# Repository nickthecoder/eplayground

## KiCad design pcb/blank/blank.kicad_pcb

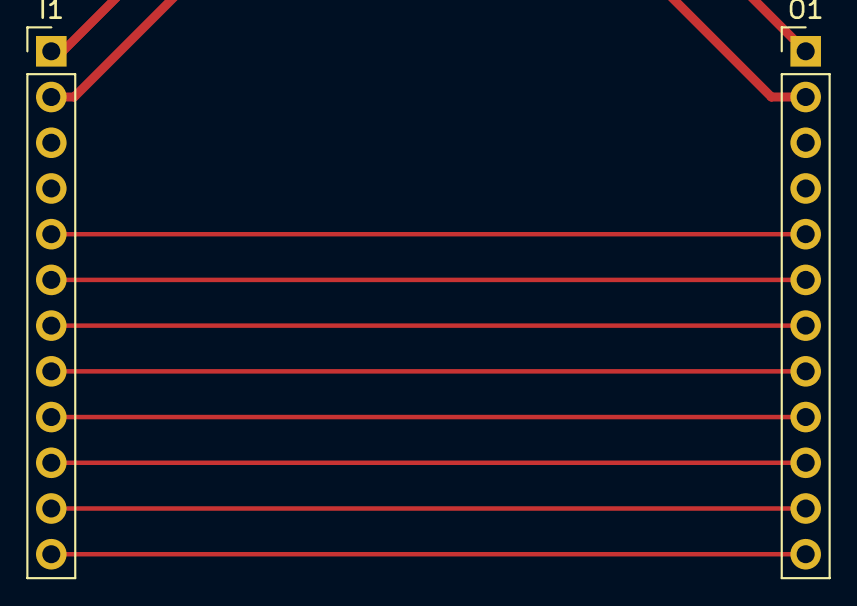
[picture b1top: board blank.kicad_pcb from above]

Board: 2 copper layers, 4 parts (0 on the bottom side), 11 nets.

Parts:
I1: Input; Pin_Header_Straight_1x12_Pitch2.54mm
M3, M3#2: MountingHole_3.2mm_M3
O1: Output; Socket_Strip_Straight_1x12_Pitch2.54mm

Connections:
/L0: I1.5, O1.5
/L1: I1.6, O1.6
/L2: I1.7, O1.7
/L3: I1.8, O1.8
/L4: I1.9, O1.9
/L5: I1.10, O1.10
/L6: I1.11, O1.11
/L7: I1.12, O1.12
/VCC: I1.2, O1.2
/VIN: I1.1, O1.1
Earth: I1.3, O1.3

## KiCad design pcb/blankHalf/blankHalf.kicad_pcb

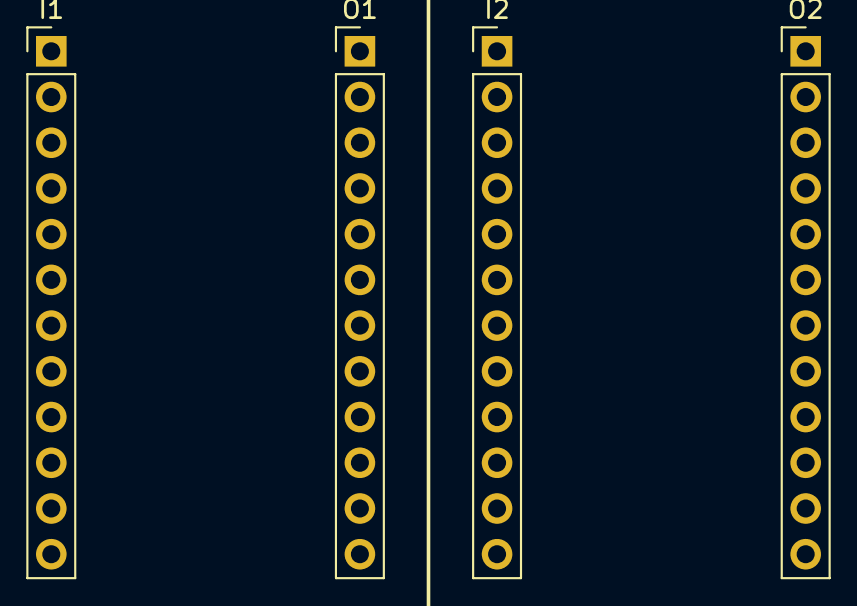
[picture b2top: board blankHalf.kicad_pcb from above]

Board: 2 copper layers, 6 parts (0 on the bottom side), 22 nets, no tracks yet.

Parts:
I1, I2: Input; Pin_Header_Straight_1x12_Pitch2.54mm
M3, M3#2: MountingHole_3.2mm_M3
O1, O2: Output; Socket_Strip_Straight_1x12_Pitch2.54mm

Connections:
/D0: I2.5, O2.5
/D1: I2.6, O2.6
/D2: I2.7, O2.7
/D3: I2.8, O2.8
/D4: I2.9, O2.9
/D5: I2.10, O2.10
/D6: I2.11, O2.11
/D7: I2.12, O2.12
/GND2: I2.3, O2.3
/L0: I1.5, O1.5
/L1: I1.6, O1.6
/L2: I1.7, O1.7
/L3: I1.8, O1.8
/L4: I1.9, O1.9
/L5: I1.10, O1.10
/L6: I1.11, O1.11
/L7: I1.12, O1.12
/VCC: I1.2, O1.2
/VCC2: I2.2, O2.2
/VIN: I1.1, O1.1
/VIN2: I2.1, O2.1
Earth: I1.3, O1.3

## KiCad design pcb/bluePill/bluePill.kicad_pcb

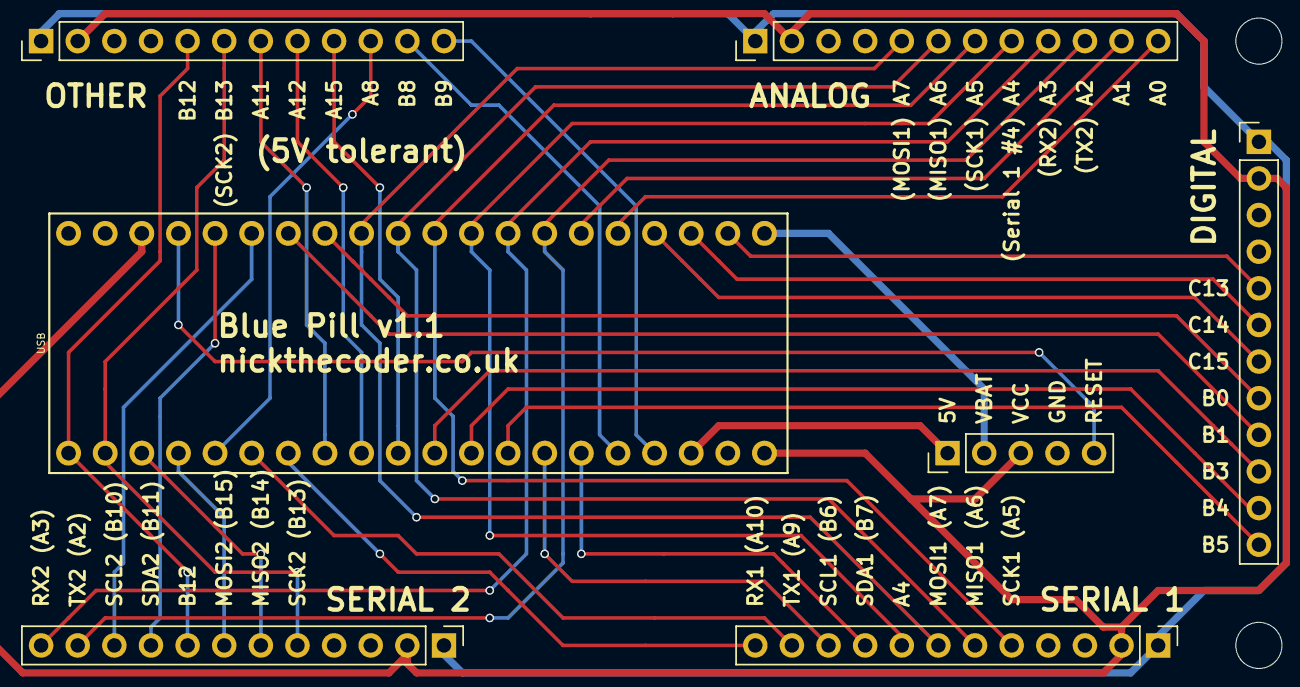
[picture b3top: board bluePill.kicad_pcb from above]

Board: 2 copper layers, 9 parts (0 on the bottom side), 38 nets.

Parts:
J3: Power; Pin_Header_Straight_1x05_Pitch2.54mm
O1, O5: SerialOutput; Socket_Strip_Straight_1x12_Pitch2.54mm
O2, O3, O4: Output; Socket_Strip_Straight_1x12_Pitch2.54mm
U1: BluePill; bluePill
X: M3; MountingHole_3.2mm_M3
X#2: M3; MountingHole_3.2mm_M3

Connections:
/5V: J3.1, U1.38
/A0: O3.12, U1.5
/A1: O3.11, U1.6
/A2: O3.10, O5.11, U1.7
/A3: O3.9, O5.12, U1.8
/A4: O1.8, O3.8, U1.9
/A5: O1.5, O3.7, U1.10
/A6: O1.6, O3.6, U1.11
/A7: O1.7, O3.5, U1.12
/A8: O4.10, U1.25
/A9: O1.11, U1.26
/A10: O1.12, U1.27
/A11: O4.7, U1.28
/A12: O4.8, U1.29
/A15: O4.9, U1.30
/B0: O2.8, U1.13
/B1: O2.9, U1.14
/B3: O2.10, U1.31
/B4: O2.11, U1.32
/B5: O2.12, U1.33
/B6: O1.10, U1.34
/B7: O1.9, U1.35
/B8: O4.11, U1.36
/B9: O4.12, U1.37
/B10: O5.10, U1.15
/B11: O5.9, U1.16
/B12: O4.5, O5.8, U1.21
/B13: O4.6, O5.5, U1.22
/B14: O5.6, U1.23
/B15: O5.7, U1.24
/C13: O2.5, U1.2
/C14: O2.6, U1.3
/C15: O2.7, U1.4
/GND: J3.4, O1.3, O2.3, O3.3, O4.3, O5.3, U1.19, U1.20, U1.39
/RESET: J3.5, U1.17
/VBAT: J3.2, U1.1
/VCC: J3.3, O1.2, O2.2, O3.2, O4.2, O5.2, U1.18, U1.40
/VIN: O1.1, O2.1, O3.1, O4.1, O5.1

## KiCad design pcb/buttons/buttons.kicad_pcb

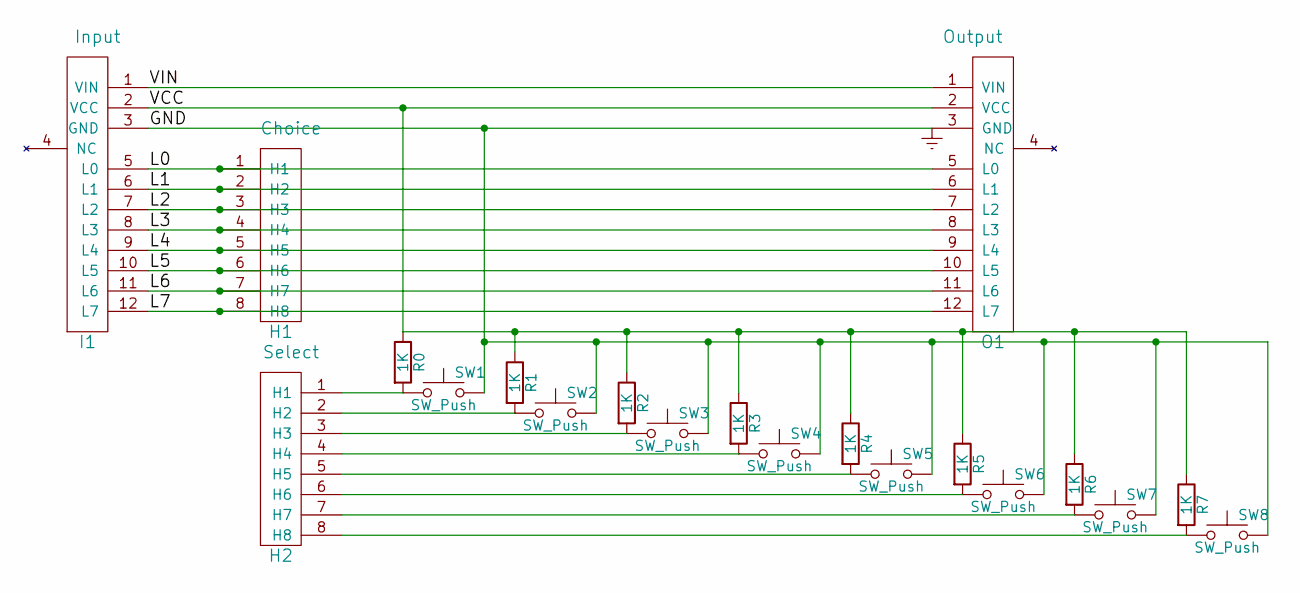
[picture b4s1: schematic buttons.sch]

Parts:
H1: Choice; Pin_Header_Straight_1x08_Pitch2.54mm
H2: Select; Pin_Header_Straight_1x08_Pitch2.54mm
I1: Input; Pin_Header_Straight_1x12_Pitch2.54mm
O1: Output; Pin_Header_Straight_1x12_Pitch2.54mm
R0, R1, R2, R3, R4, R5, R6, R7: 1K; R_Axial_DIN0204_L3.6mm_D1.6mm_P7.62mm_Horizontal
SW1, SW2, SW3, SW4, SW5, SW6, SW7, SW8: SW_Push; SW_PUSH_6mm

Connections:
/L0: H1.1 (H1), I1.5 (L0), O1.5 (L0)
/L1: H1.2 (H2), I1.6 (L1), O1.6 (L1)
/L2: H1.3 (H3), I1.7 (L2), O1.7 (L2)
/L3: H1.4 (H4), I1.8 (L3), O1.8 (L3)
/L4: H1.5 (H5), I1.9 (L4), O1.9 (L4)
/L5: H1.6 (H6), I1.10 (L5), O1.10 (L5)
/L6: H1.7 (H7), I1.11 (L6), O1.11 (L6)
/L7: H1.8 (H8), I1.12 (L7), O1.12 (L7)
/VCC: I1.2 (VCC), O1.2 (VCC), R0.1, R1.1, R2.1, R3.1, R4.1, R5.1, R6.1, R7.1
/VIN: I1.1 (VIN), O1.1 (VIN)
Earth: I1.3 (GND), O1.3 (GND), SW1.2, SW2.2, SW3.2, SW4.2, SW5.2, SW6.2, SW7.2, SW8.2
unnamed: H2.1 (H1), R0.2, SW1.1
unnamed: H2.2 (H2), R1.2, SW2.1
unnamed: H2.3 (H3), R2.2, SW3.1
unnamed: H2.4 (H4), R3.2, SW4.1
unnamed: H2.5 (H5), R4.2, SW5.1
unnamed: H2.6 (H6), R5.2, SW6.1
unnamed: H2.7 (H7), R6.2, SW7.1
unnamed: H2.8 (H8), R7.2, SW8.1

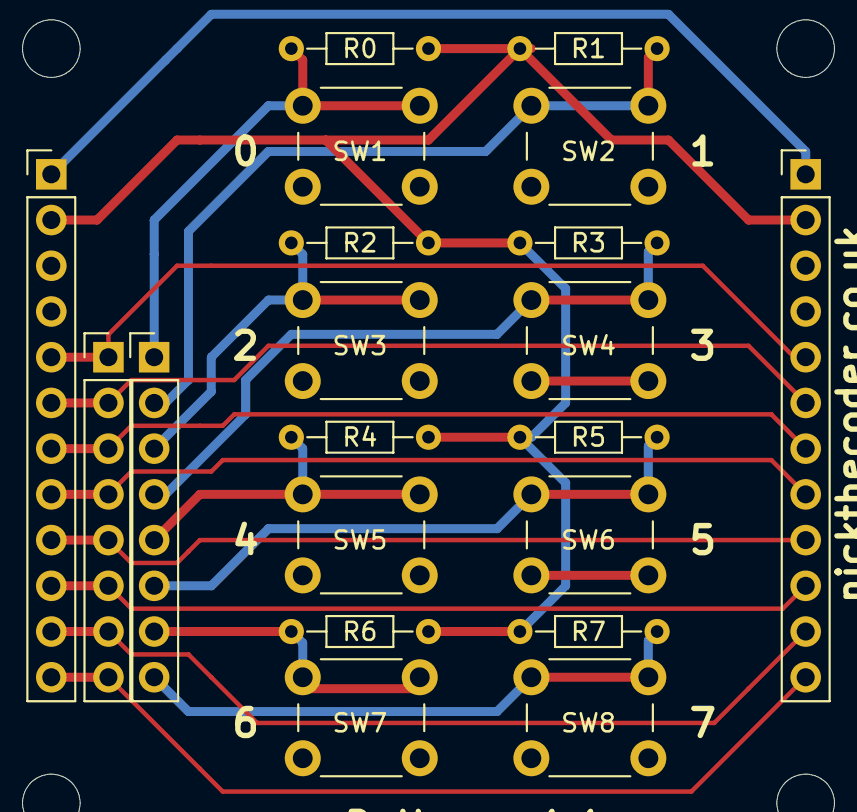
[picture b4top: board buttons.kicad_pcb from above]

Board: 2 copper layers, 22 parts (0 on the bottom side), 19 nets.

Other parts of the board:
M3, M3#2: MountingHole_3.2mm_M3

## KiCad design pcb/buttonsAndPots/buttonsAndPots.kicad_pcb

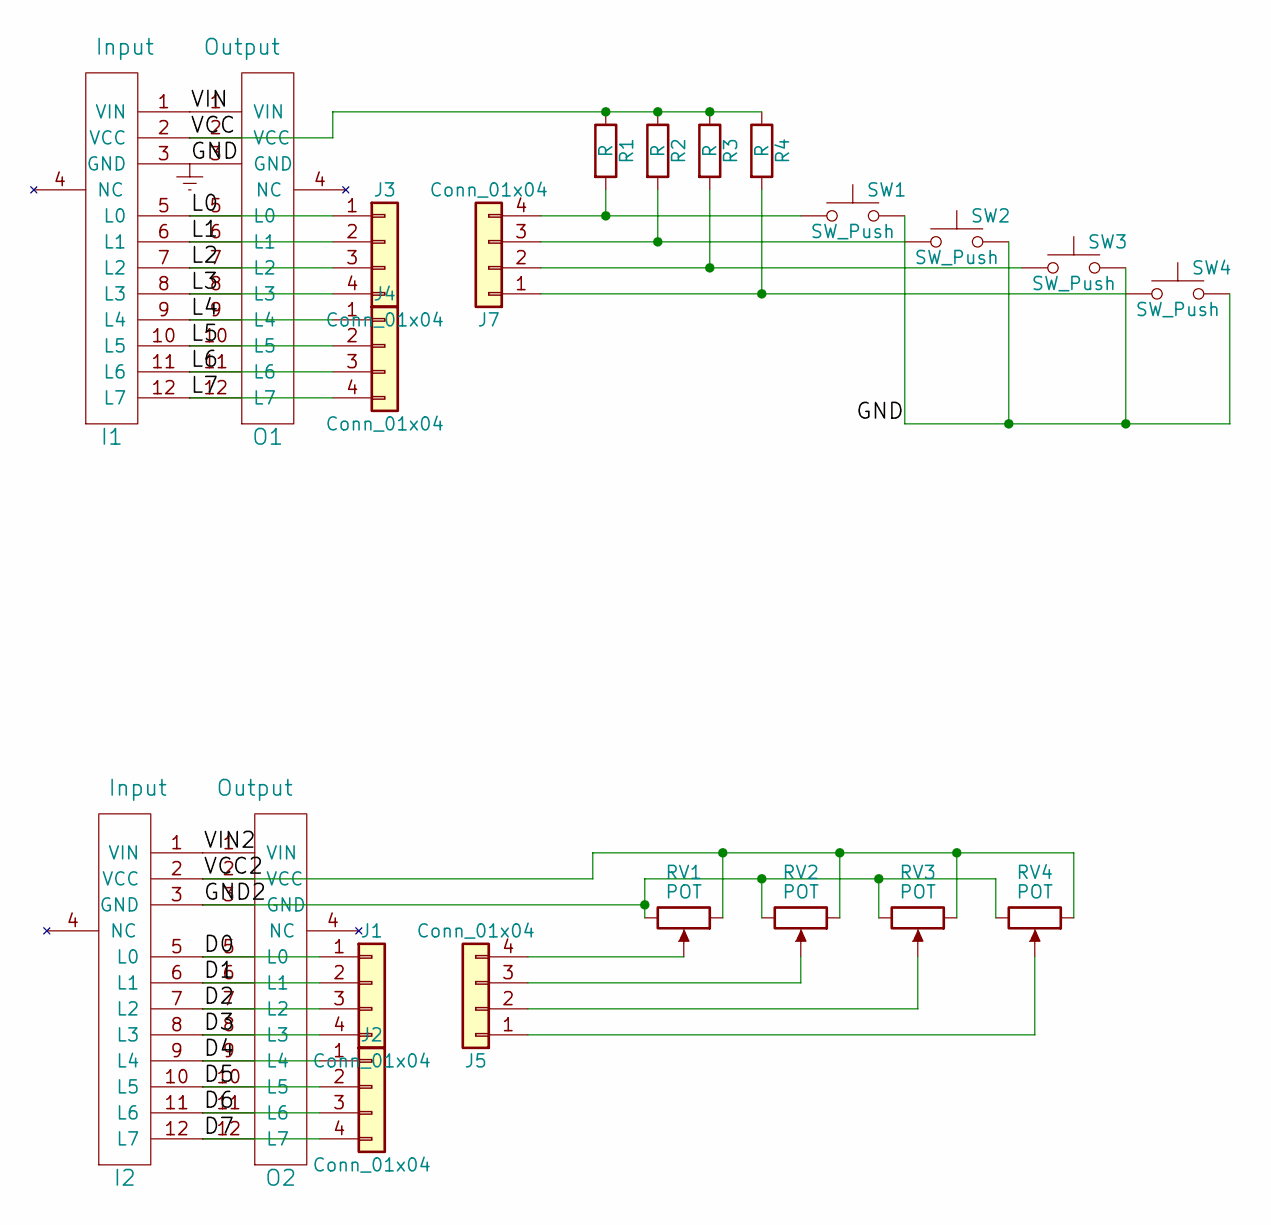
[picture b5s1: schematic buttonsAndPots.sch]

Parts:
I1, I2: Input; Pin_Header_Straight_1x12_Pitch2.54mm
J1, J2, J3, J4, J5, J7: Conn_01x04; Pin_Header_Straight_1x04_Pitch2.54mm
O1, O2: Output; Socket_Strip_Straight_1x12_Pitch2.54mm
R1, R2, R3, R4: R; R_Axial_DIN0204_L3.6mm_D1.6mm_P7.62mm_Horizontal
RV1, RV2, RV3, RV4: POT; Potentiometer_Trimmer_Piher_PT-10v10_Horizontal_Px10.0mm_Py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
SW1, SW2, SW3, SW4: SW_Push; SW_PUSH_6mm

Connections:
/D0: I2.5 (L0), J1.1, O2.5 (L0)
/D1: I2.6 (L1), J1.2, O2.6 (L1)
/D2: I2.7 (L2), J1.3, O2.7 (L2)
/D3: I2.8 (L3), J1.4, O2.8 (L3)
/D4: I2.9 (L4), J2.1, O2.9 (L4)
/D5: I2.10 (L5), J2.2, O2.10 (L5)
/D6: I2.11 (L6), J2.3, O2.11 (L6)
/D7: I2.12 (L7), J2.4, O2.12 (L7)
/GND2: I2.3 (GND), O2.3 (GND), RV1.3, RV2.3, RV3.3, RV4.3
/L0: I1.5 (L0), J3.1, O1.5 (L0)
/L1: I1.6 (L1), J3.2, O1.6 (L1)
/L2: I1.7 (L2), J3.3, O1.7 (L2)
/L3: I1.8 (L3), J3.4, O1.8 (L3)
/L4: I1.9 (L4), J4.1, O1.9 (L4)
/L5: I1.10 (L5), J4.2, O1.10 (L5)
/L6: I1.11 (L6), J4.3, O1.11 (L6)
/L7: I1.12 (L7), J4.4, O1.12 (L7)
/VCC: I1.2 (VCC), O1.2 (VCC), R1.1, R2.1, R3.1, R4.1
/VCC2: I2.2 (VCC), O2.2 (VCC), RV1.1, RV2.1, RV3.1, RV4.1
/VIN: I1.1 (VIN), O1.1 (VIN)
/VIN2: I2.1 (VIN), O2.1 (VIN)
Earth: I1.3 (GND), O1.3 (GND), SW1.2, SW2.2, SW3.2, SW4.2
unnamed: J5.1, RV4.2
unnamed: J5.2, RV3.2
unnamed: J5.3, RV2.2
unnamed: J5.4, RV1.2
unnamed: J7.1, R4.2, SW4.1
unnamed: J7.2, R3.2, SW3.1
unnamed: J7.3, R2.2, SW2.1
unnamed: J7.4, R1.2, SW1.1

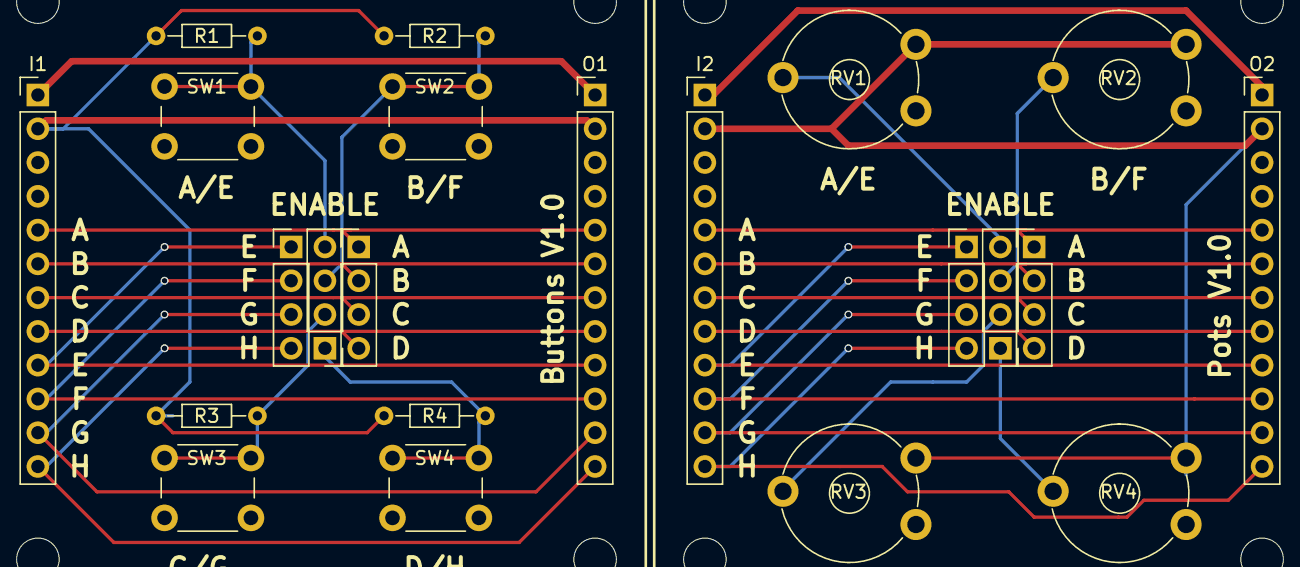
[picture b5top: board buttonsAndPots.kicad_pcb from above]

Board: 2 copper layers, 24 parts (0 on the bottom side), 30 nets.

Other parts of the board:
M3, M3#2: MountingHole_3.2mm_M3

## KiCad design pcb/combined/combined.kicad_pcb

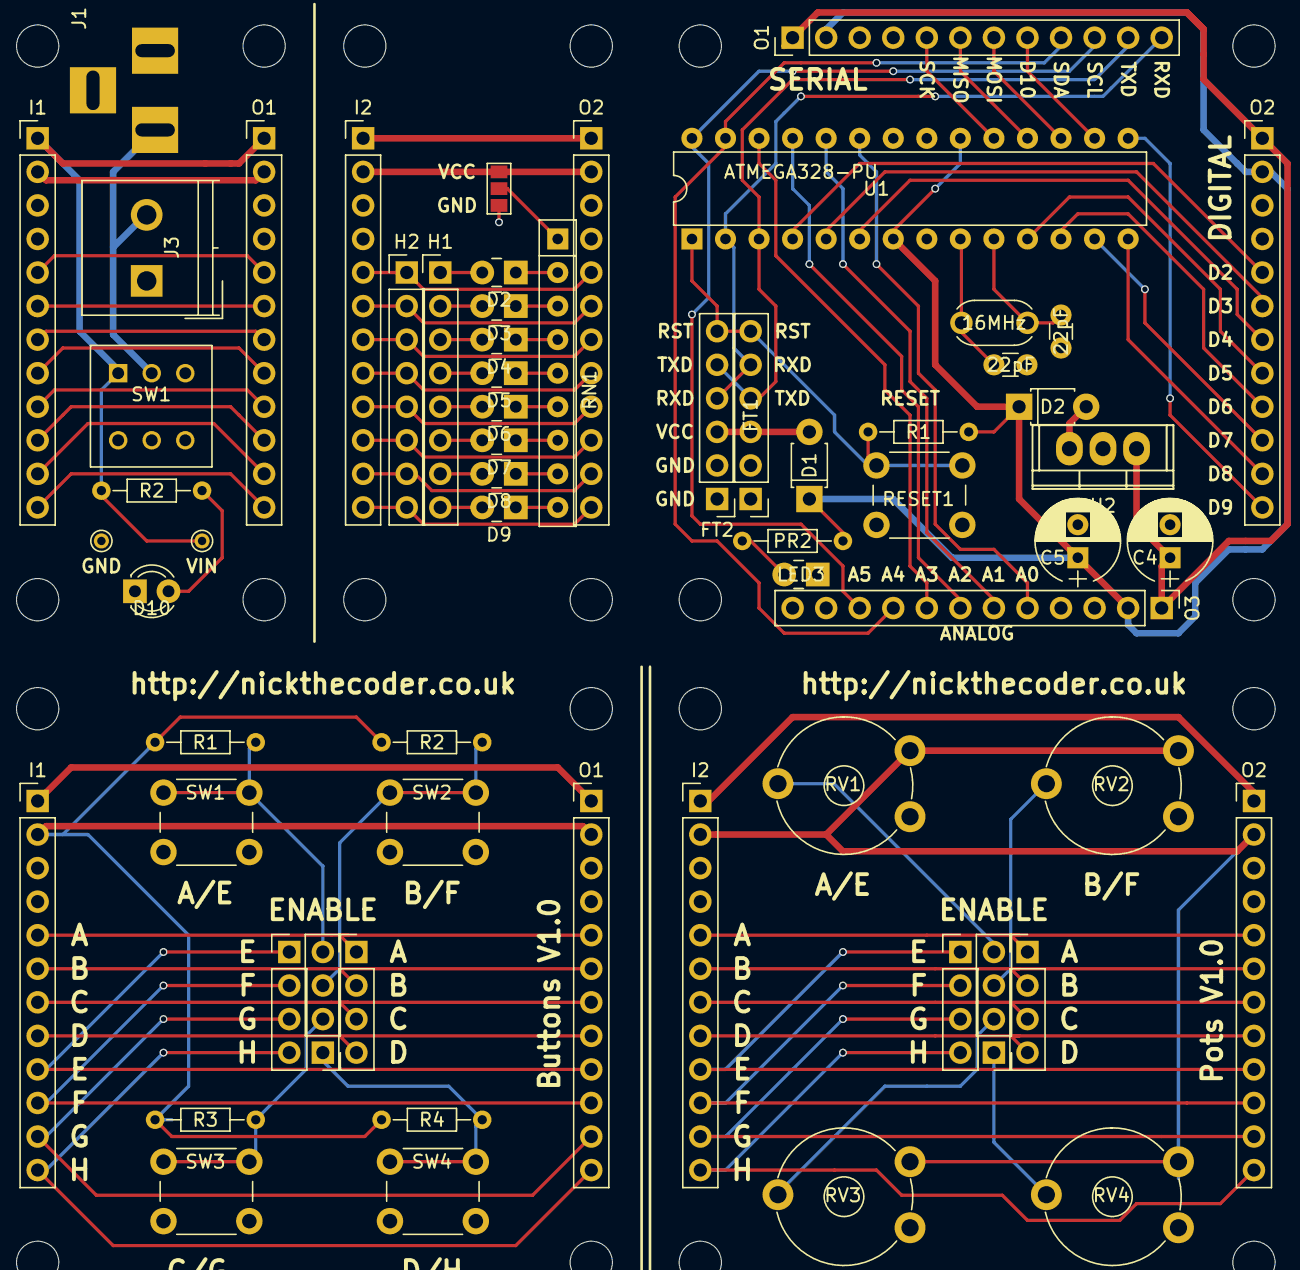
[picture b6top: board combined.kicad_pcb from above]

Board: 2 copper layers, 67 parts (0 on the bottom side), 66 nets.

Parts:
C2, C3: 22pF; C_Disc_D3.0mm_W1.6mm_P2.50mm
C4: 0.47uF; CP_Radial_D6.3mm_P2.50mm
C5: 100nF; CP_Radial_D6.3mm_P2.50mm
D1, D2#2: D; D_T-1_P5.08mm_Horizontal
D2, D3, D4, D5, D6, D7, D8, D9: LED; LED_Rectangular_W3.0mm_H2.0mm
D10: LED; LED_D3.0mm
FT1, FT2: FTDI; Pin_Header_Straight_1x06_Pitch2.54mm
H1: Headers8; Pin_Header_Straight_1x08_Pitch2.54mm
H2: Headers8L; Pin_Header_Straight_1x08_Pitch2.54mm
I1, I1#2, I2, I2#2: Input; Pin_Header_Straight_1x12_Pitch2.54mm
J1: Conn_Coaxial_Power; BARREL_JACK
J1#2, J2#2, J3#2, J4, J5, J7: Conn_01x04; Pin_Header_Straight_1x04_Pitch2.54mm
J2: GS3
J3: Screw_Terminal_01x02; TerminalBlock_Philmore_TB132_02x5mm_Straight
LED3: POWER; LED_Rectangular_W3.0mm_H2.0mm
M3, M3#2, M3#3, M3#4: MountingHole_3.2mm_M3
O1, O1#3, O2, O2#2, O2#3, O3: Output; Socket_Strip_Straight_1x12_Pitch2.54mm
O1#2: SerialOutput; Socket_Strip_Straight_1x12_Pitch2.54mm
PR2: R; R_Axial_DIN0204_L3.6mm_D1.6mm_P7.62mm_Horizontal
R1: 10K; R_Axial_DIN0204_L3.6mm_D1.6mm_P7.62mm_Horizontal
R1#2, R2, R2#2, R3, R4: R; R_Axial_DIN0204_L3.6mm_D1.6mm_P7.62mm_Horizontal
RESET1: SW_Push; SW_PUSH_6mm
RN1: R_Network08; R_Array_SIP9
RV1, RV2, RV3, RV4: POT; Potentiometer_Trimmer_Piher_PT-10v10_Horizontal_Px10.0mm_Py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
SW1: SW_SPST; SW_SPDT_8mm
SW1#2, SW2, SW3, SW4: SW_Push; SW_PUSH_6mm
TP1, TP2: TEST; PINTST
U1: ATMEGA328-PU; DIP-28_W7.62mm
U2: L7805; TO-220
Y1: 16MHz; Resonator-2pin_w6.0mm_h3.0mm

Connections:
/A0: O3.5, U1.23
/A1: O3.6, U1.24
/A2: O3.7, U1.25
/A3: O3.8, U1.26
/A4: O1#2.9, O3.9, U1.27
/A5: O1#2.10, O3.10, U1.28
/D0: FT1.5, FT2.4, H2.1, I2.5, I2#2.5, J1#2.1, O1#2.12, O2.5, O2#3.5, U1.2
/D1: FT1.4, FT2.5, H2.2, I2.6, I2#2.6, J1#2.2, O1#2.11, O2.6, O2#3.6, U1.3
/D2: H2.3, I2.7, I2#2.7, J1#2.3, O2.7, O2#2.5, O2#3.7, U1.4
/D3: H2.4, I2.8, I2#2.8, J1#2.4, O2.8, O2#2.6, O2#3.8, U1.5
/D4: H2.5, I2.9, I2#2.9, J2#2.1, O2.9, O2#2.7, O2#3.9, U1.6
/D5: H2.6, I2.10, I2#2.10, J2#2.2, O2.10, O2#2.8, O2#3.10, U1.11
/D6: H2.7, I2.11, I2#2.11, J2#2.3, O2.11, O2#2.9, O2#3.11, U1.12
/D7: H2.8, I2.12, I2#2.12, J2#2.4, O2.12, O2#2.10, O2#3.12, U1.13
/D8: O2#2.11, U1.14
/D9: O2#2.12, U1.15
/D10: O1#2.8, U1.16
/D11: O1#2.7, U1.17
/D12: O1#2.6, U1.18
/D13: O1#2.5, U1.19
/GND2: I2.3, I2#2.3, J2.3, O2.3, O2#3.3, RV1.3, RV2.3, RV3.3, RV4.3
/L0: I1.5, I1#2.5, J3#2.1, O1.5, O1#3.5
/L1: I1.6, I1#2.6, J3#2.2, O1.6, O1#3.6
/L2: I1.7, I1#2.7, J3#2.3, O1.7, O1#3.7
/L3: I1.8, I1#2.8, J3#2.4, O1.8, O1#3.8
/L4: I1.9, I1#2.9, J4.1, O1.9, O1#3.9
/L5: I1.10, I1#2.10, J4.2, O1.10, O1#3.10
/L6: I1.11, I1#2.11, J4.3, O1.11, O1#3.11
/L7: I1.12, I1#2.12, J4.4, O1.12, O1#3.12
/POWER: J1.1, J3.2, SW1.2
/RESET: FT1.6, FT2.6, R1.1, RESET1.1, U1.1
/VCC: C5.1, D1.1, D2#2.1, I1.2, I1#2.2, O1.2, O1#2.2, O1#3.2, O2#2.2, O3.2, PR2.2, R1.2, R1#2.1, R2#2.1, R3.1, R4.1, U1.7, U1.20
/VCC2: I2.2, I2#2.2, J2.1, O2.2, O2#3.2, RV1.1, RV2.1, RV3.1, RV4.1
/VIN: C4.1, I1.1, I1#2.1, O1.1, O1#2.1, O1#3.1, O2#2.1, O3.1, R2.1, SW1.1, TP1.1, U2.1
/VIN2: I2.1, I2#2.1, O2.1, O2#3.1
Earth: C2.2, C3.1, C4.2, C5.2, D10.1, FT1.1, FT1.2, FT2.1, FT2.2, I1.3, I1#2.3, J1.2, J3.1, LED3.1, O1.3, O1#2.3, O1#3.3, O2#2.3, O3.3, RESET1.2, SW1#2.2, SW2.2, SW3.2, SW4.2, TP2.1, U1.8, U1.22, U2.2
unnamed: C2.1, U1.9, Y1.2
unnamed: C3.2, U1.10, Y1.1
unnamed: D1.2, FT1.3, FT2.3
unnamed: D2.1, RN1.2
unnamed: D2.2, D2#2.2, H1.1, U2.3
unnamed: D3.1, RN1.3
unnamed: D3.2, H1.2
unnamed: D4.1, RN1.4
unnamed: D4.2, H1.3
unnamed: D5.1, RN1.5
unnamed: D5.2, H1.4
unnamed: D6.1, RN1.6
unnamed: D6.2, H1.5
unnamed: D7.1, RN1.7
unnamed: D7.2, H1.6
unnamed: D8.1, RN1.8
unnamed: D8.2, H1.7
unnamed: D9.1, RN1.9
unnamed: D9.2, H1.8
unnamed: D10.2, R2.2
unnamed: J2.2, RN1.1
unnamed: J5.1, RV4.2
unnamed: J5.2, RV3.2
unnamed: J5.3, RV2.2
unnamed: J5.4, RV1.2
unnamed: J7.1, R4.2, SW4.1
unnamed: J7.2, R3.2, SW3.1
unnamed: J7.3, R2#2.2, SW2.1
unnamed: J7.4, R1#2.2, SW1#2.1
unnamed: LED3.2, PR2.1
